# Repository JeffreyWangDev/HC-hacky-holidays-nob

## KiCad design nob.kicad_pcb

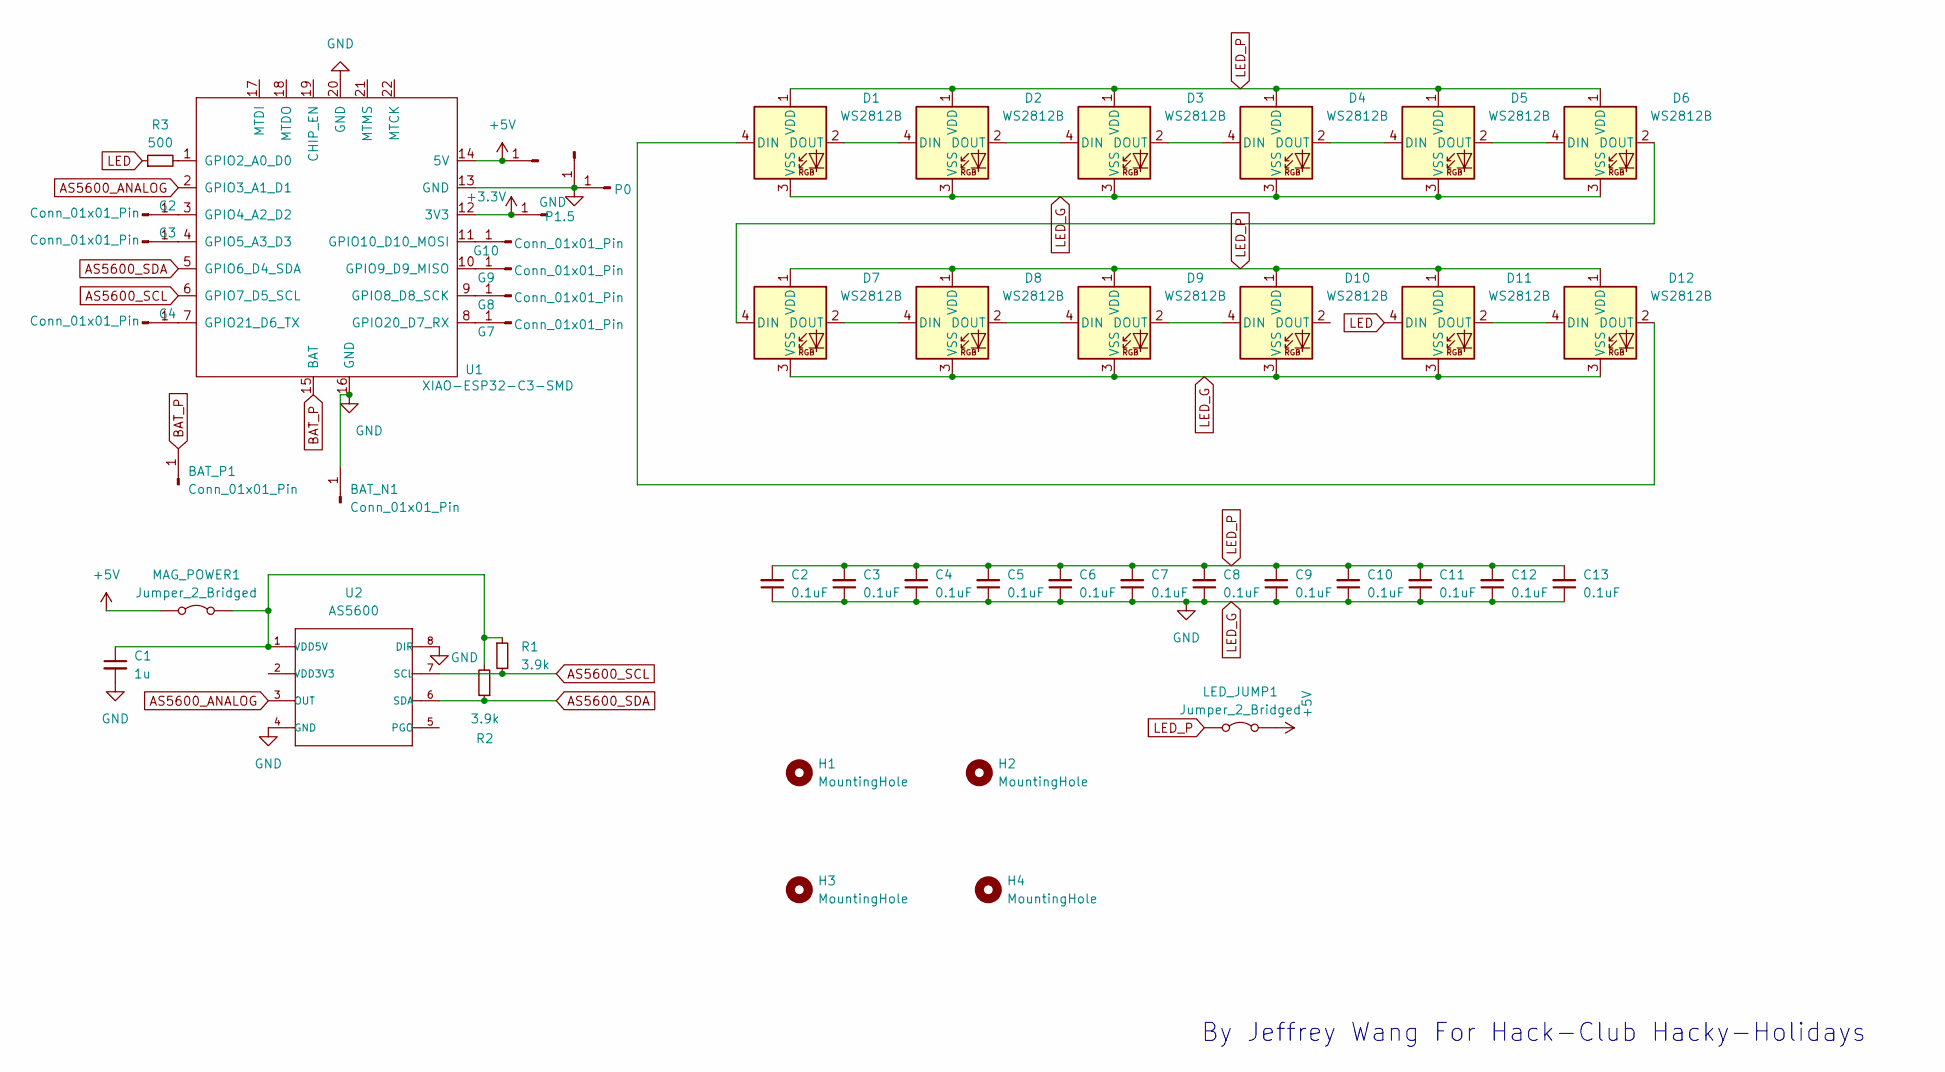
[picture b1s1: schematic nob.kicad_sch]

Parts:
BAT_N1: Conn_01x01_Pin; SolderWire-0.5sqmm_1x01_D0.9mm_OD2.1mm
BAT_P1: Conn_01x01_Pin; SolderWire-0.5sqmm_1x01_D0.9mm_OD2.1mm
C1: 1u; C_0603_1608Metric; LCSC C15849
C2, C3, C4, C5, C6, C7, C8, C9, C10, C11, C12, C13: 0.1uF; C_0805_2012Metric; LCSC C49678
D1, D2, D3, D4, D5, D6, D7, D8, D9, D10, D11, D12: WS2812B; LED_WS2812B_PLCC4_5.0x5.0mm_P3.2mm; LCSC C114586
G2, G3, G4, G7, G8, G9, G10: Conn_01x01_Pin; SolderWire-0.1sqmm_1x01_D0.4mm_OD1mm
H1, H2, H3, H4: MountingHole; MountingHole_3.2mm_M3_DIN965_Pad_TopBottom
LED_JUMP1: Jumper_2_Bridged; SolderJumper-2_P1.3mm_Bridged2Bar_Pad1.0x1.5mm
MAG_POWER1: Jumper_2_Bridged; SolderJumper-2_P1.3mm_Bridged2Bar_Pad1.0x1.5mm
P0, P1, P1.5, P10: Conn_01x01_Pin; SolderWire-0.1sqmm_1x01_D0.4mm_OD1mm
R1, R2: 3.9k; R_0805_2012Metric; LCSC C17614
R3: 500; C_0805_2012Metric; LCSC C17408
U1: XIAO-ESP32-C3-SMD; XIAO-ESP32C3-SMD
U2: AS5600; LCSC C499458

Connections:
+3.3V: P1.5.1, U1.12 (3V3)
+5V: LED_JUMP1.2 (B), MAG_POWER1.1 (A), P1.1, U1.14 (5V)
AS5600_ANALOG: U1.2 (GPIO3_A1_D1), U2.3 (OUT)
AS5600_SCL: R1.2, U1.6 (GPIO7_D5_SCL), U2.7 (SCL)
AS5600_SDA: R2.1, U1.5 (GPIO6_D4_SDA), U2.6 (SDA)
BAT_P: BAT_P1.1, U1.15 (BAT)
LED: D11.4 (DIN), R3.1
LED_G: BAT_N1.1, C1.2, C2.1, C3.1, C4.1, C5.1, C6.1, C7.1, C8.1, C9.1, C10.1, C11.1, C12.1, C13.1, D1.3 (VSS), D2.3 (VSS), D3.3 (VSS), D4.3 (VSS), D5.3 (VSS), D6.3 (VSS), D7.3 (VSS), D8.3 (VSS), D9.3 (VSS), D10.3 (VSS), D11.3 (VSS), D12.3 (VSS), P0.1, P10.1, U1.13 (GND), U1.16 (GND), U1.20 (GND), U2.4 (GND), U2.8 (DIR)
LED_P: C2.2, C3.2, C4.2, C5.2, C6.2, C7.2, C8.2, C9.2, C10.2, C11.2, C12.2, C13.2, D1.1 (VDD), D2.1 (VDD), D3.1 (VDD), D4.1 (VDD), D5.1 (VDD), D6.1 (VDD), D7.1 (VDD), D8.1 (VDD), D9.1 (VDD), D10.1 (VDD), D11.1 (VDD), D12.1 (VDD), LED_JUMP1.1 (A)
unnamed: D1.4 (DIN), D12.2 (DOUT)
unnamed: D1.2 (DOUT), D2.4 (DIN)
unnamed: D2.2 (DOUT), D3.4 (DIN)
unnamed: D3.2 (DOUT), D4.4 (DIN)
unnamed: D4.2 (DOUT), D5.4 (DIN)
unnamed: D5.2 (DOUT), D6.4 (DIN)
unnamed: D6.2 (DOUT), D7.4 (DIN)
unnamed: D7.2 (DOUT), D8.4 (DIN)
unnamed: D8.2 (DOUT), D9.4 (DIN)
unnamed: D9.2 (DOUT), D10.4 (DIN)
unnamed: D11.2 (DOUT), D12.4 (DIN)
unnamed: G2.1, U1.3 (GPIO4_A2_D2)
unnamed: G3.1, U1.4 (GPIO5_A3_D3)
unnamed: G4.1, U1.7 (GPIO21_D6_TX)
unnamed: G7.1, U1.8 (GPIO20_D7_RX)
unnamed: G8.1, U1.9 (GPIO8_D8_SCK)
unnamed: G9.1, U1.10 (GPIO9_D9_MISO)
unnamed: G10.1, U1.11 (GPIO10_D10_MOSI)
unnamed: C1.1, MAG_POWER1.2 (B), R1.1, R2.2, U2.1 (VDD5V)
unnamed: R3.2, U1.1 (GPIO2_A0_D0)

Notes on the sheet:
By Jeffrey Wang For Hack-Club Hacky-Holidays

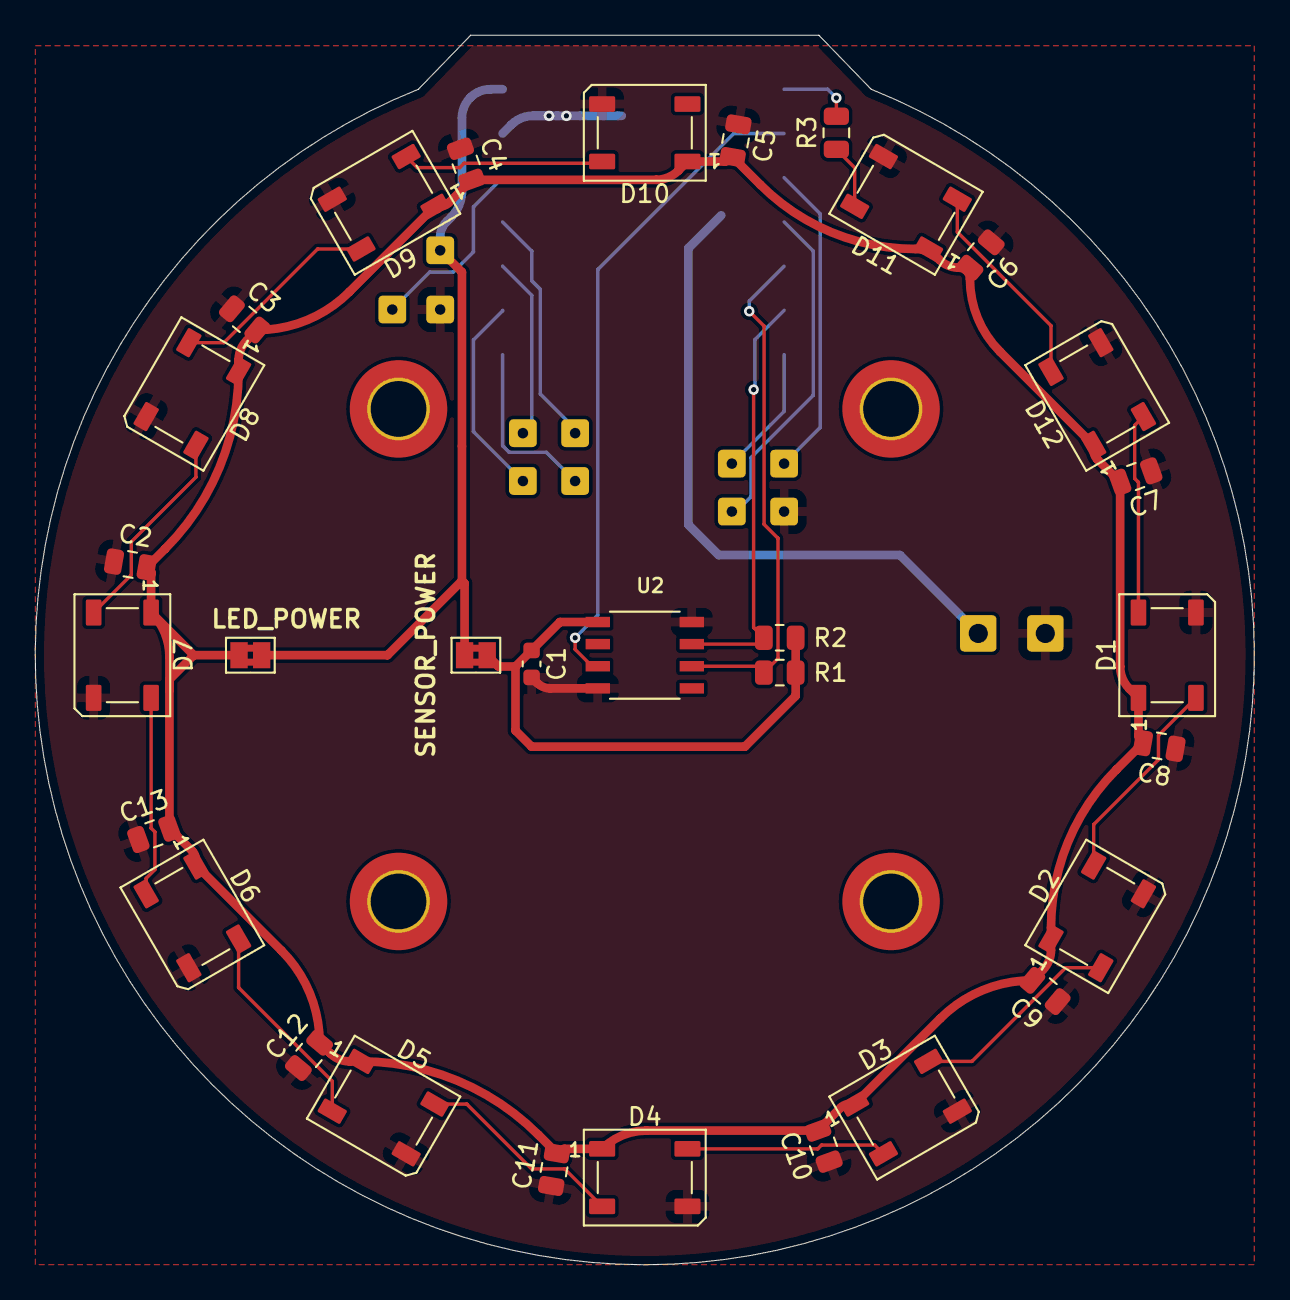
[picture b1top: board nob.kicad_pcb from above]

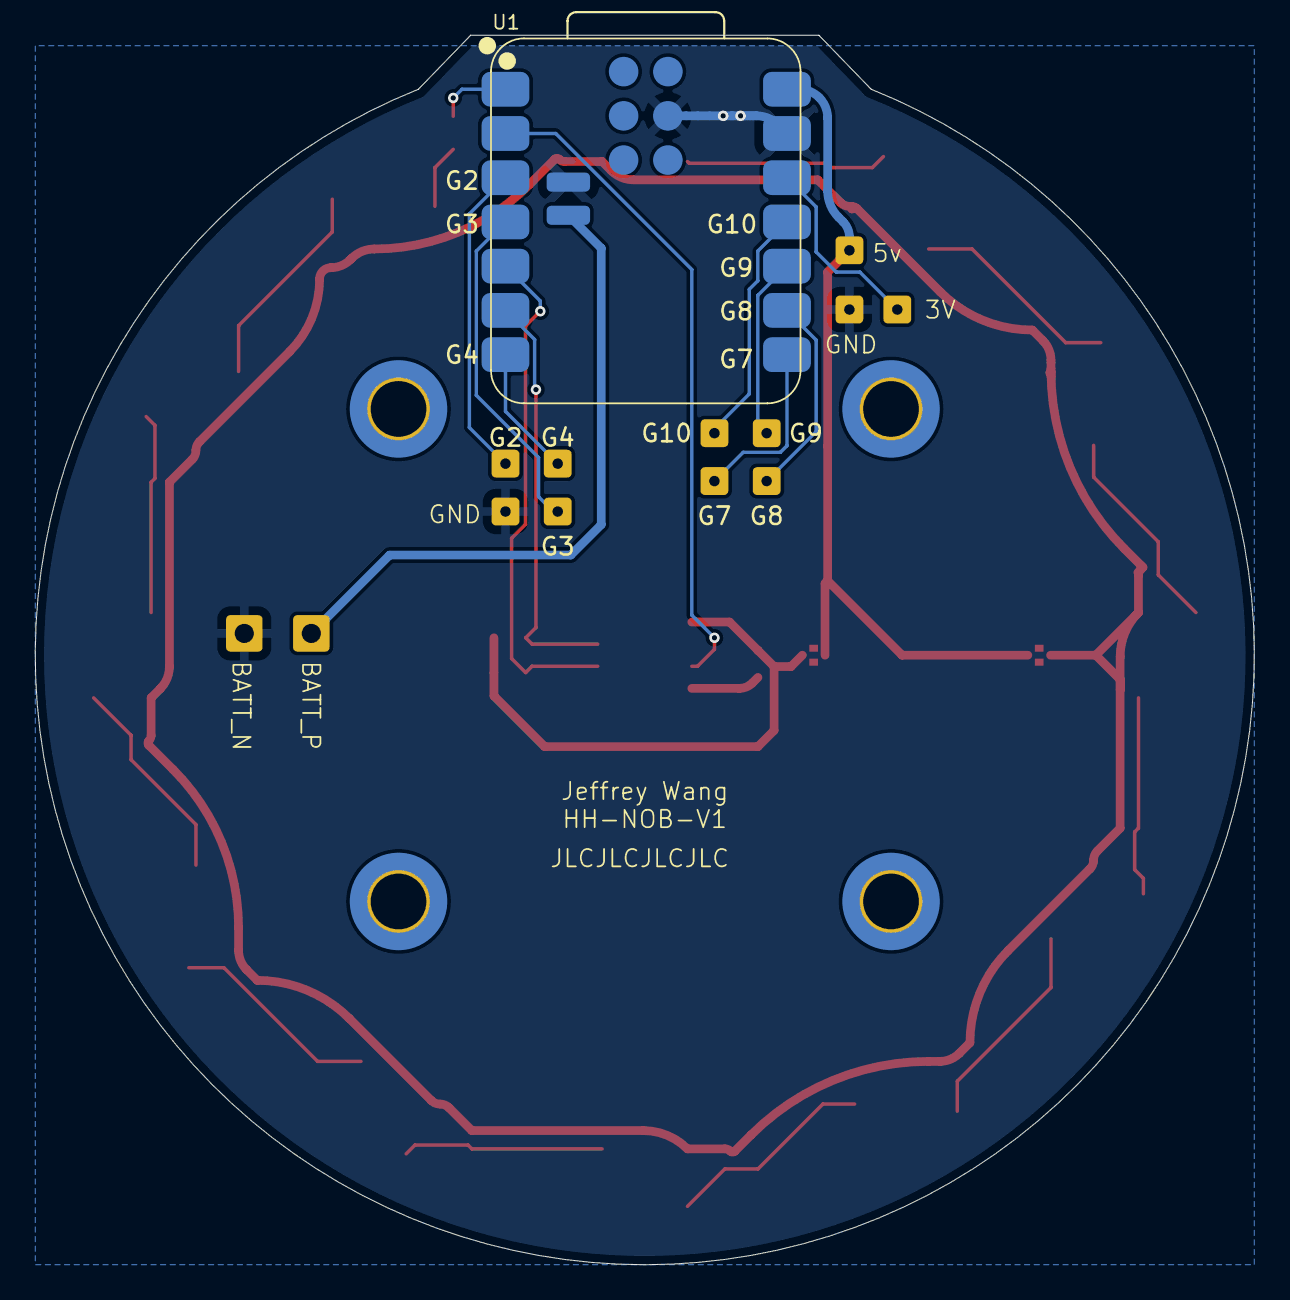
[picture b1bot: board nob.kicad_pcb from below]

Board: 2 copper layers, 70.0 x 70.6 mm, 49 parts (14 on the bottom side), 29 nets.

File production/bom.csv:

Designator,Footprint,Quantity,Value,LCSC Part #
"BAT_N1, BAT_P1, G10, G2, G3, G4, G7, G8, G9, P0, P1, P1.5, P10",SolderWire-0.1sqmm_1x01_D0.4mm_OD1mm,13,Conn_01x01_Pin,
C1,0603,1,1u,C15849
"C10, C11, C12, C13, C2, C3, C4, C5, C6, C7, C8, C9",0805,12,0.1uF,C49678
"D1, D10, D11, D12, D2, D3, D4, D5, D6, D7, D8, D9",LED_WS2812B_PLCC4_5.0x5.0mm_P3.2mm,12,WS2812B,C114586
"R1, R2",0805,2,3.9k,C17614
R3,0805,1,500,C17408
U1,XIAO-ESP32C3-SMD,1,XIAO-ESP32-C3-SMD,
U2,AS5600,1,AS5600,C499458

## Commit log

2024-12-28 init
